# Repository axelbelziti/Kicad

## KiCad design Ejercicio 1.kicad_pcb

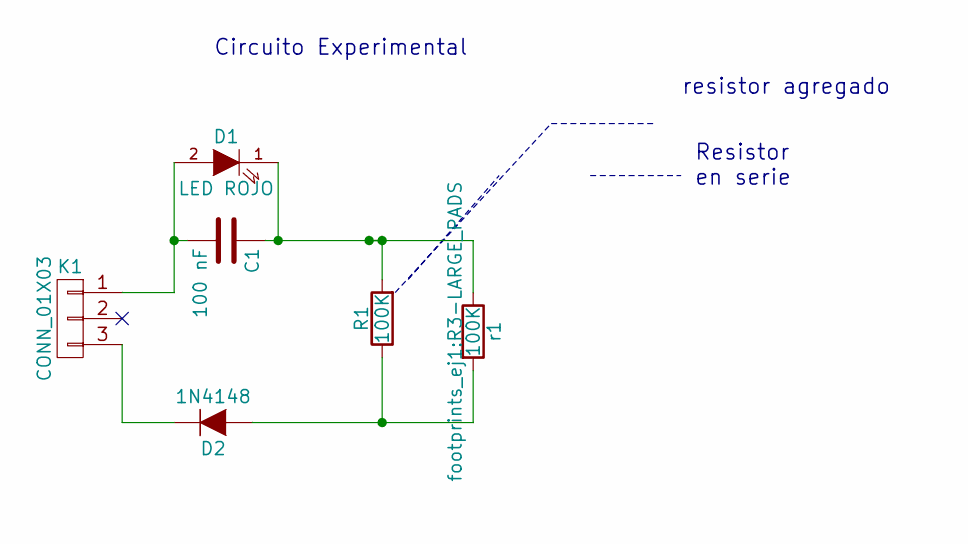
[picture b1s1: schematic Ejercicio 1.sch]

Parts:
1N4148: D2; Diode_DO-35_SOD27_Horizontal_RM10
C1: 100 nF; C_Rect_L7_W3.5_P5
D1: LED ROJO; LED-3MM
K1: CONN_01X03; bornier3
R1: 100K; R3-LARGE_PADS
r1: 100K; R3-LARGE_PADS

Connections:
unnamed: 1N4148.1 (K), K1.3
unnamed: 1N4148.2 (A), R1.1, r1.2
unnamed: C1.1, D1.1 (K), R1.2, r1.1
unnamed: C1.2, D1.2 (A), K1.1

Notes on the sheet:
Resistor en serie
Circuito Experimental
resistor agregado

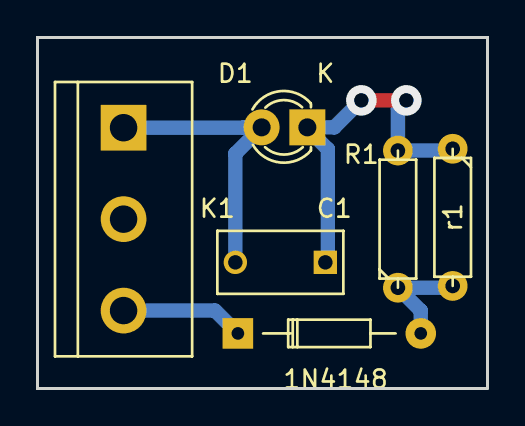
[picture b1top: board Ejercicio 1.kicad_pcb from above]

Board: 2 copper layers, 25.0 x 19.5 mm, 6 parts (0 on the bottom side), 4 nets.
